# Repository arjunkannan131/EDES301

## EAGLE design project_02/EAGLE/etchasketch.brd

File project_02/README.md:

# Etch-a-Sketch PCB – EDES301 Project 02

**Student:** Arjun Kannan  
**Course:** ENGI/EDES301   
**Due Date:** May 6, 2025  
**Instructor:** Dr. Erik Welsh

## Project Overview

This project implements a custom Printed Circuit Board (PCB) for a digital "Etch-a-Sketch" device using a PocketBeagle microcontroller. The design includes user input through potentiometers and buttons, output via an SPI display, and RGB LEDs to enhance interactivity. The board is designed in Eagle, following all required design rules and constraints.

## Hardware Components

| Component                    | Function                                   |
|------------------------------|--------------------------------------------|
| PocketBeagle                 | Central processing unit                    |
| Adafruit SPI Display (#1770) | Graphical output display via SPI           |
| 2 Potentiometers             | Control X and Y movement (analog input)    |
| 2 Buttons                    | Reset display and change drawing color     |
| 3 RGB LEDs                   | Visual feedback for selected color         |
| USB Host Port                | Expansion or future debugging interface    |

## MacroFab Manufacturing

The PCB was uploaded to MacroFab for DFM review and quoting. 

**Price Quotes (Unit Volumes):**  
- 1 Unit: $$298.50  
- 10 Units: $636.57 
- 100 Units: $1,797.05 
- 1000 Units: $12,586.26

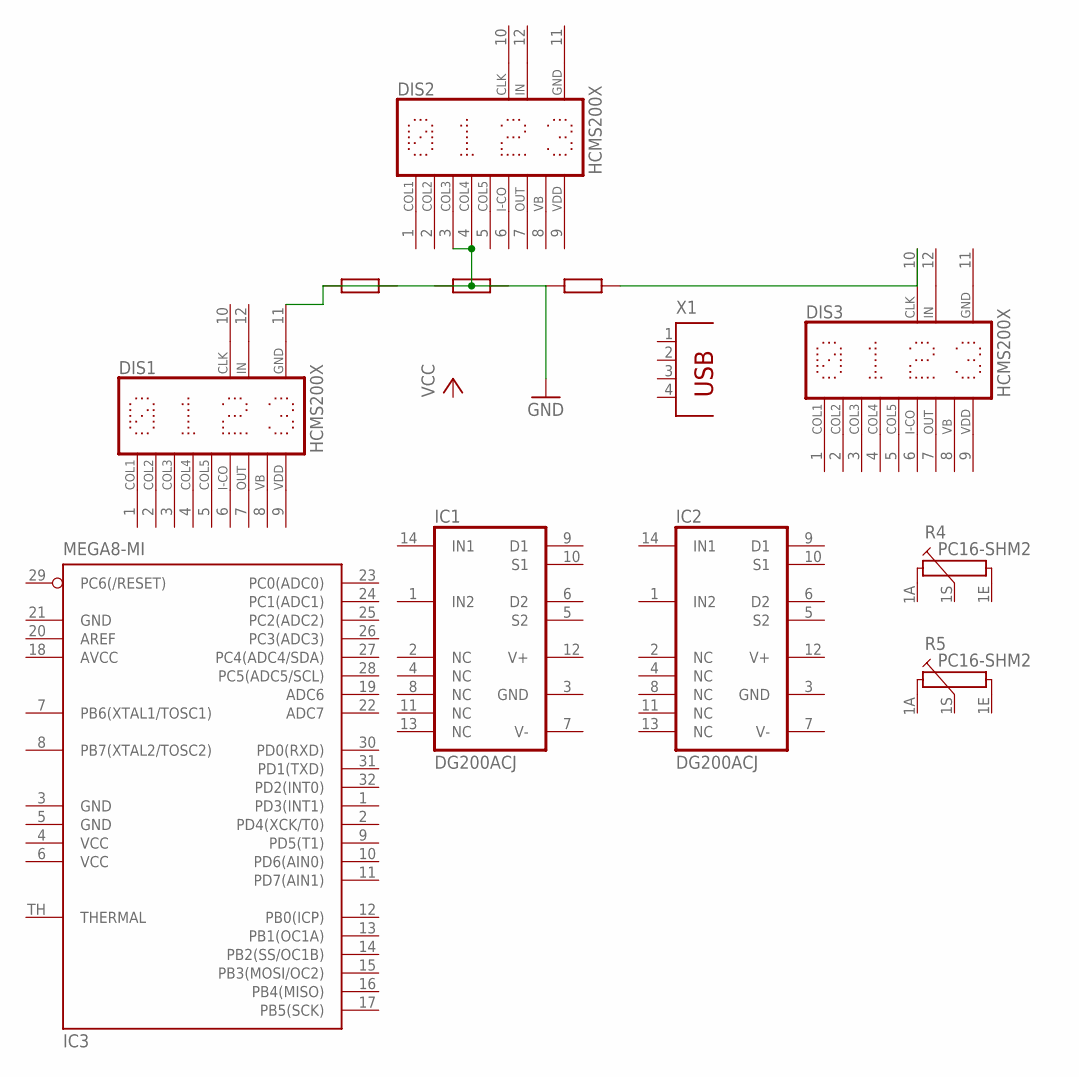
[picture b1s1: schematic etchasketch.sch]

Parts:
DIS1, DIS2, DIS3: HCMS200X
IC1, IC2: DG200ACJ; DIL14
IC3: MEGA8-MI; MLF32-TH
R4, R5: PC16-SHM2
X1: PN61729

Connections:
AVCC: IC3.18 (AVCC)
GND: DIS1.11 (GND), DIS2.3 (COL3), DIS2.4 (COL4), DIS2.11 (GND), DIS3.11 (GND), IC1.3 (GND), IC2.3 (GND), IC3.3 (GND), IC3.5 (GND), IC3.21 (GND)
V+: IC1.12 (V+), IC2.12 (V+)
V-: IC1.7 (V-), IC2.7 (V-)
VCC: IC3.4 (VCC), IC3.6 (VCC)
VDD: DIS1.9 (VDD), DIS2.9 (VDD), DIS3.9 (VDD)

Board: 2 copper layers, 9 parts (0 on the bottom side), 5 nets, no tracks yet.

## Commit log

2025-02-19 Create blink_led
2025-02-19 Create simple_calc
2025-05-05 Create test
2025-05-07 Add files via upload
    Bill of Materials
